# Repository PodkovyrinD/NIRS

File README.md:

# NIRS

в lib/WIFIRE/  лежит библиотека с элементами, которые пришлось нарисовать самому. Позже сделаю посадочные места для них.

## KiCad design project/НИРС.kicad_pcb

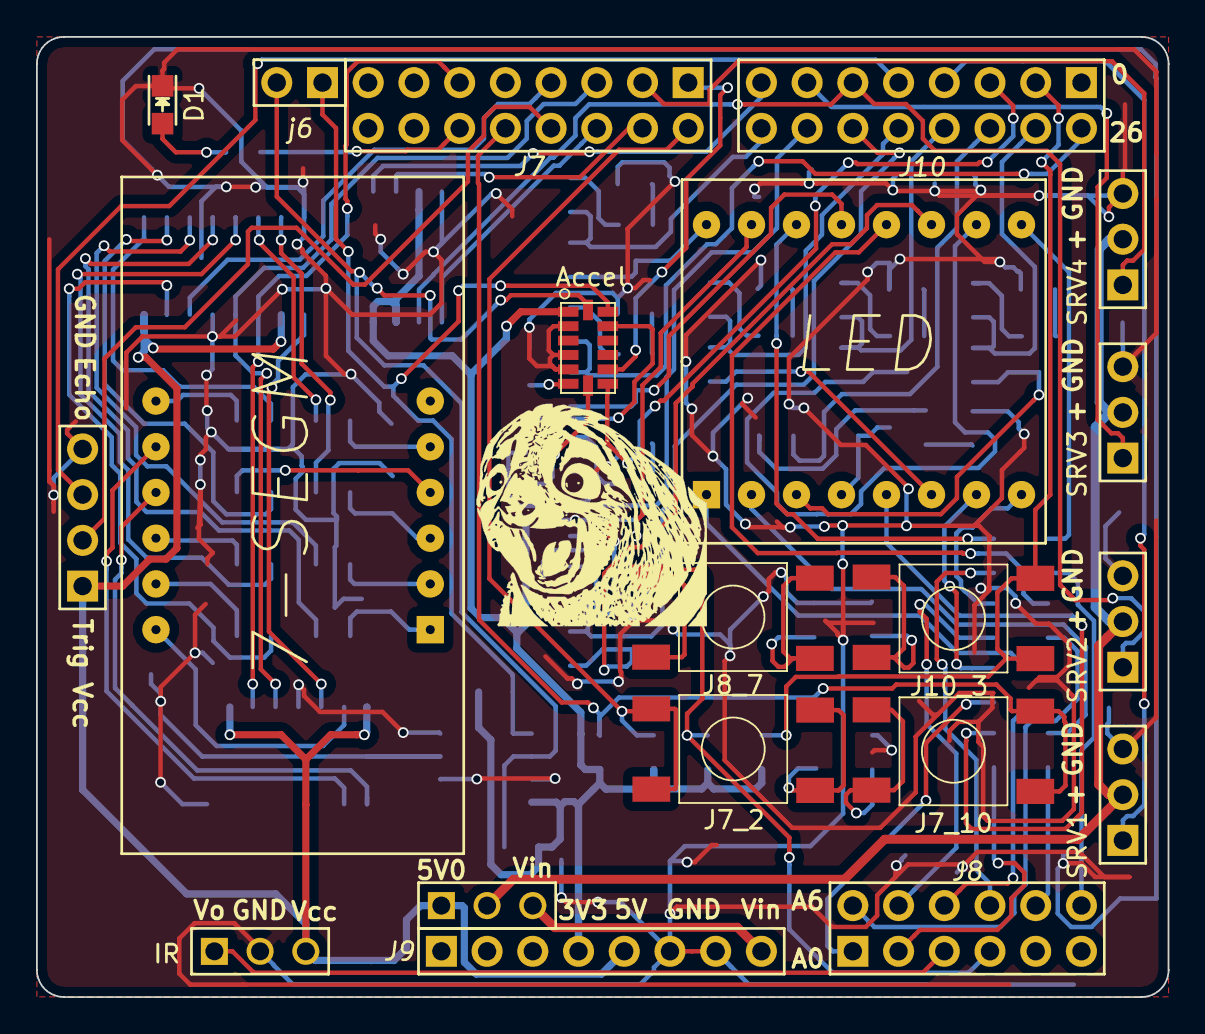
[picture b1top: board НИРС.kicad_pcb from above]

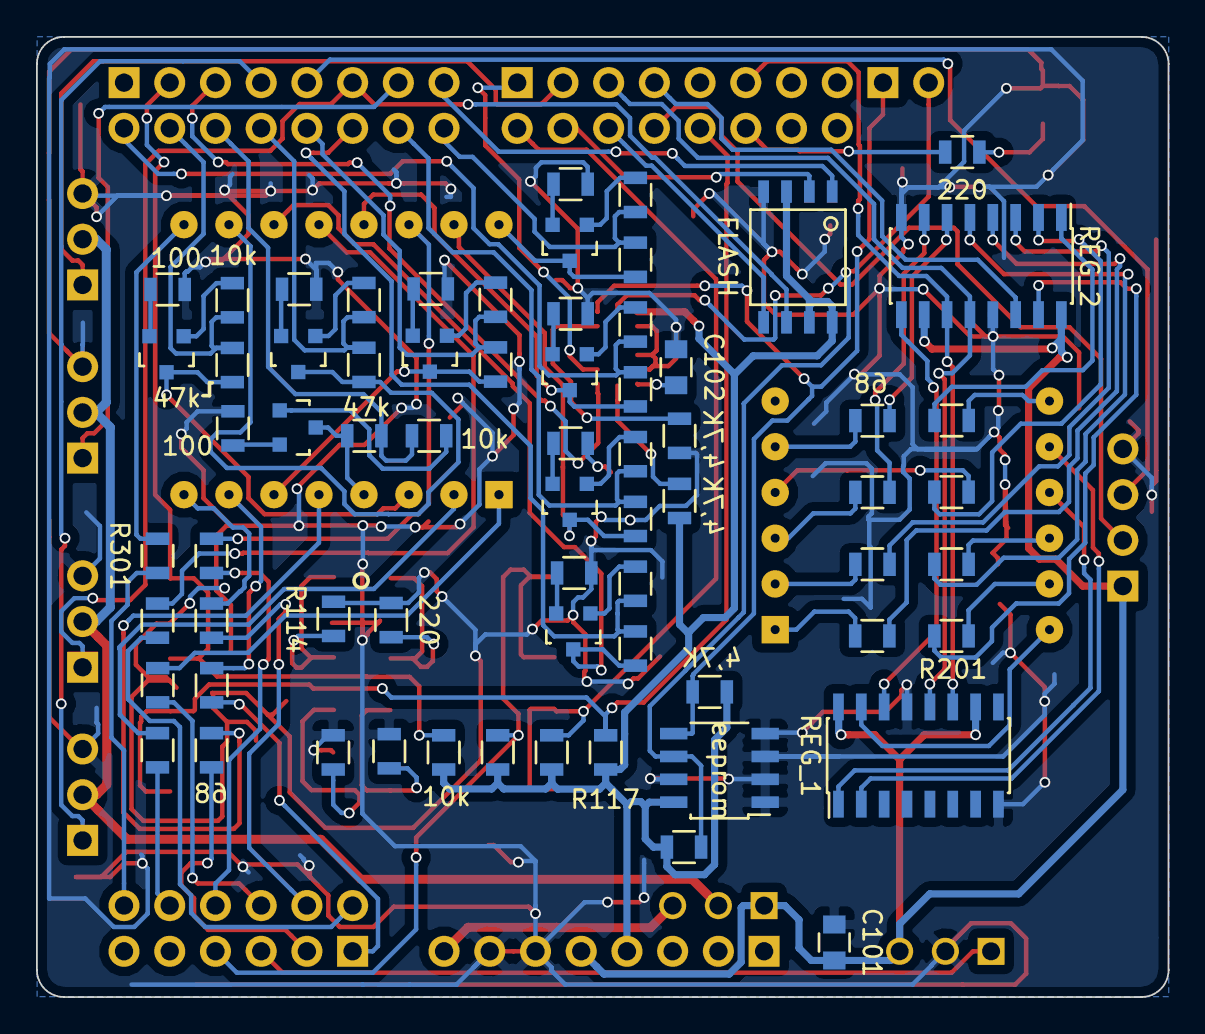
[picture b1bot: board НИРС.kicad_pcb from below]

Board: 2 copper layers, 62.9 x 53.3 mm, 87 parts (67 on the bottom side), 103 nets.

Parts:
7-SEGM: BA56-12SRWA(2); BA56-12SRWA
Accel: ADXL345
C101, C102: 10uF; C_0805
D1: LED; LED_0805
FLASH: W25Q32BV; SOIC-8(.208mil)new
IR: GP2Y0A21YK; CONN_1-3
J7: J7; CONN_J7
J7_2, J7_10, J8_7, J10_3: Button; BUTTON
J8: J8; CONN_J8
J9: J9; CONN_J9
J10: J10; CONN_J10
JMPR: JUMPER3; CONN_1-3
LED: GNM-7881AUE; GNM-7881
Q301, Q302, Q303, Q304, Q305, Q306, Q307, Q308: Tran_8050; SOT-23
R102: 4.7k; R_0805
R104: 4.7K; R_0805
R109, R110: 4,7K; R_0805
R111, R114, R115, R118, R119: 220; R_0805
R112, R113, R116, R117: 10K; R_0805
R201, R202, R203, R204, R205, R206, R207, R208, R301, R302, R303, R304, R305, R306, R307, R308: 68; R_0805
R309, R311, R315, R317, R321, R323, R327, R329: 47K; R_0805
R310, R312, R316, R318, R322, R324, R328, R330: 10k; R_0805
R313, R314, R319, R320, R325, R326, R331, R332: 100; R_0805
REG_1, REG_2: 74HC595; SOIC-16_3.9x9.9mm_Pitch1.27mm
SRV1, SRV2, SRV3, SRV4: CONN_servo
URM: HC-SR04
eeprom: AT24C64A-10PU-2.7; JEDEC_SOIC
j6: J6; CONN_J6

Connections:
+3V3: Accel.1, FLASH.3, FLASH.7, FLASH.8, J9.4, R102.1, R109.2, R110.2, R112.1, R113.1, R116.1, R117.1, eeprom.8
+5V: C101.2, IR.3, J9.5, JMPR.1, REG_1.10, REG_1.16, REG_2.10, REG_2.16, URM.1
/7-SEGM/Dig1: 7-SEGM.12, REG_1.15
/7-SEGM/Dig2: 7-SEGM.9, REG_1.1
/7-SEGM/Dig3: 7-SEGM.8, REG_1.2
/7-SEGM/QA: 7-SEGM.11, R201.2
/7-SEGM/QB: 7-SEGM.7, R202.2
/7-SEGM/QC: 7-SEGM.4, R203.2
/7-SEGM/QD: 7-SEGM.2, R204.2
/7-SEGM/QE: 7-SEGM.1, R205.2
/7-SEGM/QF: 7-SEGM.10, R206.2
/7-SEGM/QG: 7-SEGM.5, R207.2
/7-SEGM/QH: 7-SEGM.3, R208.2
/7-SEGM/RCLK: J7.5, REG_1.12, REG_2.12
/7-SEGM/SER: J7.7, REG_2.14
/7-SEGM/SRCLK: J7.11, REG_1.11, REG_2.11
/BTN_1: J10.3, J10_3.1, J10_3.2, R112.2
/BTN_2: J8.7, J8_7.1, J8_7.2, R113.2
/BTN_3: J7.2, J7_2.1, J7_2.2, R116.2
/BTN_4: J7.10, J7_10.1, J7_10.2, R117.2
/Echo: J10.9, URM.3
/INT_1: Accel.8, J10.5
/INT_2: Accel.9, J7.1
/J8_A2: IR.1, J8.5
/LED/COL1: J10.2, R311.1, R312.2
/LED/COL2: J10.4, R317.1, R318.2
/LED/COL3: J10.6, R323.1, R324.2
/LED/COL4: J10.8, R329.1, R330.2
/LED/COL5: J10.10, R327.1, R328.2
/LED/COL6: J10.12, R321.1, R322.2
/LED/COL7: J10.14, R315.1, R316.2
/LED/COL8: J10.16, R309.1, R310.2
/LED/GNM_3: LED.3, Q304.3, R317.2
/LED/GNM_4: LED.4, Q306.3, R323.2
/LED/GNM_6: LED.6, Q307.3, R327.2
/LED/GNM_10: LED.10, Q308.3, R329.2
/LED/GNM_11: LED.11, Q305.3, R321.2
/LED/GNM_13: LED.13, Q302.3, R311.2
/LED/GNM_15: LED.15, Q303.3, R315.2
/LED/GNM_16: LED.16, Q301.3, R309.2
/LED/ROW1: J8.12, R301.1
/LED/ROW2: J8.8, R302.1
/LED/ROW3: J8.4, R303.1
/LED/ROW4: J8.2, R304.1
/LED/ROW5: J8.6, R305.1
/LED/ROW6: J8.1, R306.1
/LED/ROW7: J8.10, R307.1
/LED/ROW8: J8.3, R308.1
/PIN_5: FLASH.6, J10.11, SRV2.1
/PIN_7: FLASH.1, J10.15
/PIN_35: FLASH.2, J7.4
/PIN_36: FLASH.5, J7.6
/PWM1: J10.7, SRV1.1
/PWM3: J10.13, SRV3.1
/PWM4: J7.3, SRV4.1
/PWR: JMPR.2, SRV1.2, SRV2.2, SRV3.2, SRV4.2
/SCL: Accel.14, R110.1, eeprom.6, j6.2
/SDA: Accel.13, R109.1, eeprom.5, j6.1
/Trig: J7.8, URM.2
/Vin: J9.8, JMPR.3
GND: Accel.2, Accel.4, Accel.5, C101.1, C102.1, D1.1, FLASH.4, IR.2, J9.6, J9.7, R104.1, R114.2, R115.2, R118.2, R119.2, R313.1, R314.1, R319.1, R320.1, R325.1, R326.1, R331.1, R332.1, REG_1.8, REG_1.13, REG_2.8, REG_2.13, SRV1.3, SRV2.3, SRV3.3, SRV4.3, URM.4, eeprom.1, eeprom.2, eeprom.3, eeprom.4, eeprom.7
unnamed: Accel.6, C102.2
unnamed: Accel.7, R102.2
unnamed: Accel.12, R104.2
unnamed: J10_3.3, J10_3.4, R114.1
unnamed: J8_7.3, J8_7.4, R115.1
unnamed: J7_2.3, J7_2.4, R118.1
unnamed: J7_10.3, J7_10.4, R119.1
unnamed: D1.2, R111.2
unnamed: J7.12, R111.1
unnamed: LED.1, R305.2
unnamed: LED.2, R307.2
unnamed: LED.5, R308.2
unnamed: LED.7, R306.2
unnamed: LED.8, R303.2
unnamed: LED.9, R301.2
unnamed: LED.12, R304.2
unnamed: LED.14, R302.2
unnamed: Q301.1, R310.1
unnamed: Q301.2, R313.2
unnamed: Q302.1, R312.1
unnamed: Q302.2, R314.2
unnamed: Q303.1, R316.1
unnamed: Q303.2, R319.2
unnamed: Q304.1, R318.1
unnamed: Q304.2, R320.2
unnamed: Q305.1, R322.1
unnamed: Q305.2, R325.2
unnamed: Q306.1, R324.1
unnamed: Q306.2, R326.2
unnamed: Q307.1, R328.1
unnamed: Q307.2, R331.2
unnamed: Q308.1, R330.1
unnamed: Q308.2, R332.2
unnamed: R201.1, REG_2.15
unnamed: R202.1, REG_2.1
unnamed: R203.1, REG_2.2
unnamed: R204.1, REG_2.3
unnamed: R205.1, REG_2.4
unnamed: R206.1, REG_2.5
unnamed: R207.1, REG_2.6
unnamed: R208.1, REG_2.7
unnamed: REG_1.14, REG_2.9

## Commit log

2016-03-16 Added files via upload
2016-03-16 Rename WIFIRE.bak to lib/WIFIRE/WIFIRE.bak
2016-03-16 Rename WIFIRE.bck to lib/WIFIRE/WIFIRE.bck
2016-03-16 Rename WIFIRE.dcm to lib/WIFIRE/WIFIRE.dcm
2016-03-16 Rename WIFIRE.lib to lib/WIFIRE/WIFIRE.lib
2016-03-16 Rename НИРС.bak to project/НИРС.bak
2016-03-16 Rename НИРС.pro to project/НИРС.pro
2016-03-16 Rename НИРС.sch to project/НИРС.sch
2016-04-08 Rename BA56-12SRWA.kicad_mod to WIFIRE.pretty/BA56-12SRWA.kicad_mod
2016-04-08 Rename project/BA56-12SRWA.kicad_mod to project/.pretty/BA56-12SRWA.kicad_mod
2016-04-08 Rename project/CONN_J10.kicad_mod to project/.pretty/CONN_J10.kicad_mod
2016-04-08 Rename project/CONN_J6.kicad_mod to project/.pretty/CONN_J6.kicad_mod
2016-04-08 Rename project/CONN_J7.kicad_mod to project/.pretty/CONN_J7.kicad_mod
2016-04-08 Rename project/CONN_J8.kicad_mod to project/.pretty/CONN_J8.kicad_mod
2016-04-08 Rename project/CONN_J9.kicad_mod to project/.pretty/CONN_J9.kicad_mod
2016-04-08 Rename project/CONN_servo.kicad_mod to project/.pretty/CONN_servo.kicad_mod
2016-04-08 Rename project/GNM-7881.kicad_mod to project/.pretty/GNM-7881.kicad_mod
2016-04-08 Rename project/HC-SR04.kicad_mod to project/.pretty/HC-SR04.kicad_mod
2016-04-30 Rename НИРС-B.Cu.ps to Postscript/НИРС-B.Cu.ps
2016-04-30 Rename НИРС-B.SilkS.ps to Postscript/НИРС-B.SilkS.ps
2016-04-30 Rename НИРС-F.Cu.ps to Postscript/НИРС-F.Cu.ps
2016-04-30 Rename НИРС-F.SilkS.ps to Postscript/НИРС-F.SilkS.ps
2016-05-24 Rename BA56-12SRWA.kicad_mod to project/.pretty/BA56-12SRWA.kicad_mod
2016-05-24 Rename BUTTON.kicad_mod to project/.pretty/BUTTON.kicad_mod
2016-05-24 Rename CONN_1-3.kicad_mod to project/.pretty/CONN_1-3.kicad_mod
2016-05-24 Rename CONN_J10.kicad_mod to project/.pretty/CONN_J10.kicad_mod
2016-05-24 Rename CONN_J6.kicad_mod to project/.pretty/CONN_J6.kicad_mod
2016-05-24 Rename CONN_J7.kicad_mod to project/.pretty/CONN_J7.kicad_mod
2016-05-24 Rename CONN_J8.kicad_mod to project/.pretty/CONN_J8.kicad_mod
2016-05-24 Rename CONN_J9.kicad_mod to project/.pretty/CONN_J9.kicad_mod
2016-05-24 Rename CONN_servo.kicad_mod to project/.pretty/CONN_servo.kicad_mod
2016-05-24 Rename GNM-7881.kicad_mod to project/.pretty/GNM-7881.kicad_mod
2016-05-24 Rename HC-SR04.kicad_mod to project/.pretty/HC-SR04.kicad_mod
2016-05-24 Rename JEDEC_SOIC.kicad_mod to project/.pretty/JEDEC_SOIC.kicad_mod
2016-05-24 Rename LOGO.kicad_mod to project/.pretty/LOGO.kicad_mod
2016-05-24 Rename LOGO2.kicad_mod to project/.pretty/LOGO2.kicad_mod
2016-05-24 Rename LOGO3.kicad_mod to project/.pretty/LOGO3.kicad_mod
2016-05-24 Rename LOGO4.kicad_mod to project/.pretty/LOGO4.kicad_mod
2016-05-24 Rename RESET.kicad_mod to project/.pretty/RESET.kicad_mod
2016-05-24 Rename SOIC-8(.208mil).kicad_mod to project/.pretty/SOIC-8(.208mil).kicad_mod
2016-05-24 Rename SOIC-8(.208mil)new.kicad_mod to project/.pretty/SOIC-8(.208mil)new.kicad_mod
2016-05-24 Rename TS-A2PS-130.kicad_mod to project/.pretty/TS-A2PS-130.kicad_mod
